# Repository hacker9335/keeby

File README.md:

## Keeby

A custom 98-key mechanical keyboard: KiCad PCB design + QMK/VIA firmware,
built around a Raspberry Pi Pico and an MCP23017 I2C GPIO expander for
extra column pins.

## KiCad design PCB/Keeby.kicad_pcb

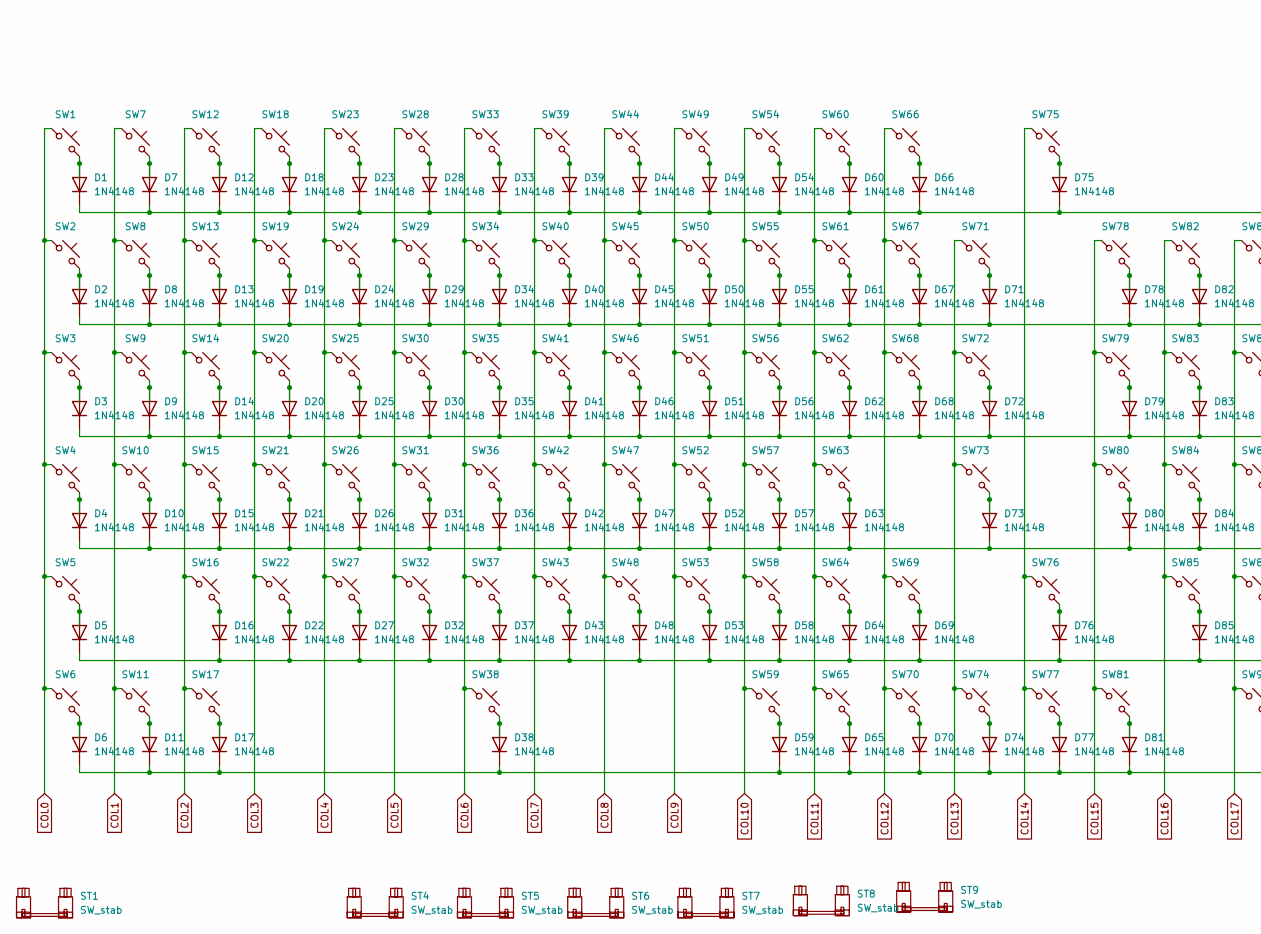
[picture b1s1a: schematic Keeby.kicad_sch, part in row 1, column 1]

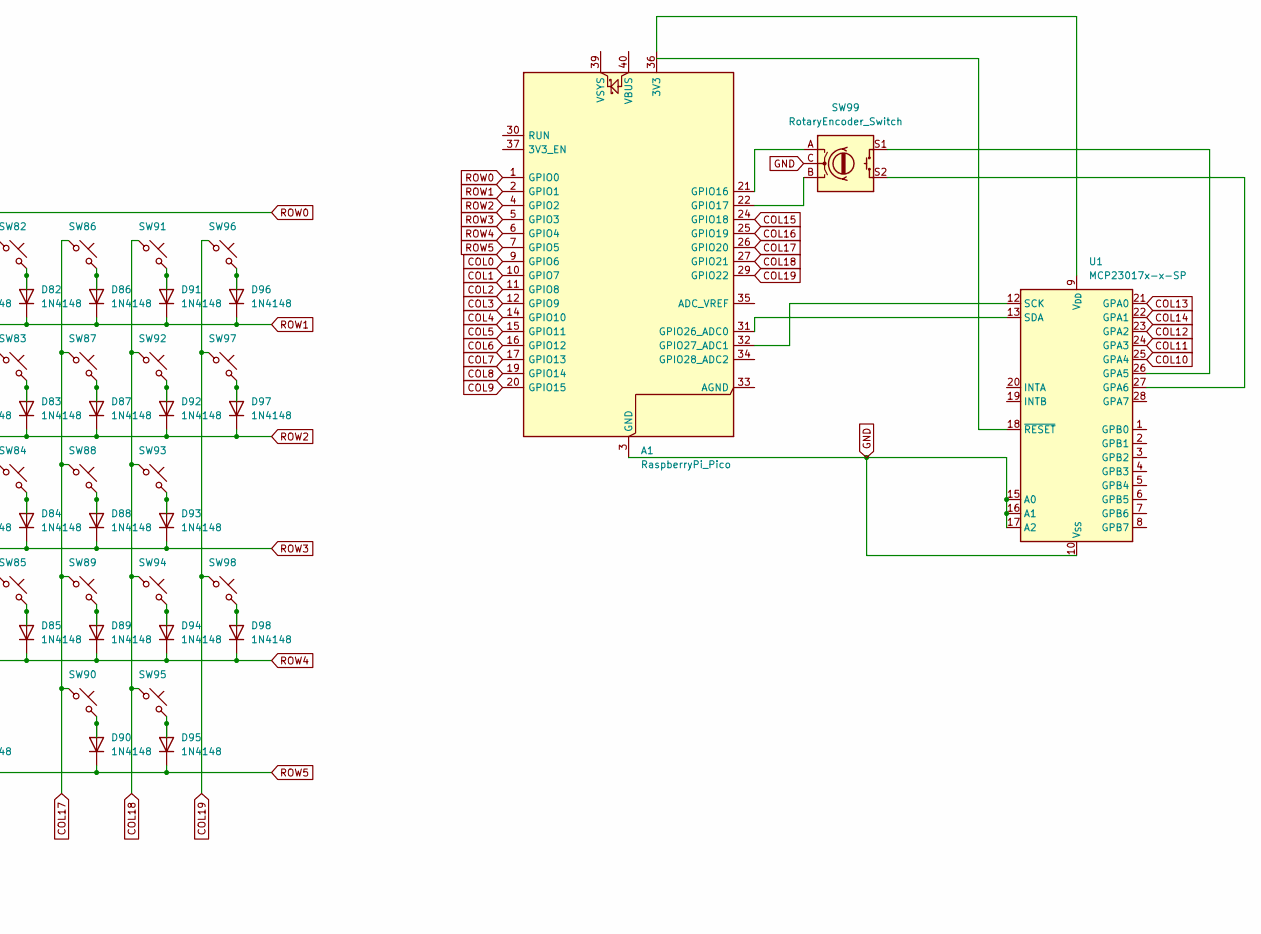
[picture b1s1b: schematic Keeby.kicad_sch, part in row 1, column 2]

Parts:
A1: RaspberryPi_Pico; RaspberryPi_Pico_Common_Unspecified
D1, D2, D3, D4, D5, D6, D7, D8, D9, D10, D11, D12, D13, D14, D15, D16, D17, D18, D19, D20, D21, D22, D23, D24, D25, D26, D27, D28, D29, D30, D31, D32, D33, D34, D35, D36, D37, D38, D39, D40, D41, D42, D43, D44, D45, D46, D47, D48, D49, D50, D51, D52, D53, D54, D55, D56, D57, D58, D59, D60, D61, D62, D63, D64, D65, D66, D67, D68, D69, D70, D71, D72, D73, D74, D75, D76, D77, D78, D79, D80, D81, D82, D83, D84, D85, D86, D87, D88, D89, D90, D91, D92, D93, D94, D95, D96, D97, D98: 1N4148; D_DO-35_SOD27_P7.62mm_Horizontal
ST1, ST4, ST5, ST6, ST7, ST8: SW_stab; STAB_MX_2u
ST9: SW_stab; STAB_MX_6.25u
SW1, SW2, SW3, SW4, SW5, SW6, SW7, SW8, SW9, SW10, SW11, SW12, SW13, SW14, SW15, SW16, SW17, SW18, SW19, SW20, SW21, SW22, SW23, SW24, SW25, SW26, SW27, SW28, SW29, SW30, SW31, SW32, SW33, SW34, SW35, SW36, SW37, SW38, SW39, SW40, SW41, SW42, SW43, SW44, SW45, SW46, SW47, SW48, SW49, SW50, SW51, SW52, SW53, SW54, SW55, SW56, SW57, SW58, SW59, SW60, SW61, SW62, SW63, SW64, SW65, SW66, SW67, SW68, SW69, SW70, SW71, SW72, SW73, SW74, SW75, SW76, SW77, SW78, SW79, SW80, SW81, SW82, SW83, SW84, SW85, SW86, SW87, SW88, SW89, SW90, SW91, SW92, SW93, SW94, SW95, SW96, SW97, SW98: SW_Push; SW_Cherry_MX_1.00u_PCB
SW99: RotaryEncoder_Switch; RotaryEncoder_Alps_EC11E-Switch_Vertical_H20mm_MountingHoles
U1: MCP23017x-x-SP; SSOP-28_5.3x10.2mm_P0.65mm

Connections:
COL0: A1.9 (GPIO6), SW1.1, SW2.1, SW3.1, SW4.1, SW5.1, SW6.1
COL1: A1.10 (GPIO7), SW7.1, SW8.1, SW9.1, SW10.1, SW11.1
COL2: A1.11 (GPIO8), SW12.1, SW13.1, SW14.1, SW15.1, SW16.1, SW17.1
COL3: A1.12 (GPIO9), SW18.1, SW19.1, SW20.1, SW21.1, SW22.1
COL4: A1.14 (GPIO10), SW23.1, SW24.1, SW25.1, SW26.1, SW27.1
COL5: A1.15 (GPIO11), SW28.1, SW29.1, SW30.1, SW31.1, SW32.1
COL6: A1.16 (GPIO12), SW33.1, SW34.1, SW35.1, SW36.1, SW37.1, SW38.1
COL7: A1.17 (GPIO13), SW39.1, SW40.1, SW41.1, SW42.1, SW43.1
COL8: A1.19 (GPIO14), SW44.1, SW45.1, SW46.1, SW47.1, SW48.1
COL9: A1.20 (GPIO15), SW49.1, SW50.1, SW51.1, SW52.1, SW53.1
COL10: SW54.1, SW55.1, SW56.1, SW57.1, SW58.1, SW59.1, U1.25 (GPA4)
COL11: SW60.1, SW61.1, SW62.1, SW63.1, SW64.1, SW65.1, U1.24 (GPA3)
COL12: SW66.1, SW67.1, SW68.1, SW69.1, SW70.1, U1.23 (GPA2)
COL13: SW71.1, SW72.1, SW73.1, SW74.1, U1.21 (GPA0)
COL14: SW75.1, SW76.1, SW77.1, U1.22 (GPA1)
COL15: A1.24 (GPIO18), SW78.1, SW79.1, SW80.1, SW81.1
COL16: A1.25 (GPIO19), SW82.1, SW83.1, SW84.1, SW85.1
COL17: A1.26 (GPIO20), SW86.1, SW87.1, SW88.1, SW89.1, SW90.1
COL18: A1.27 (GPIO21), SW91.1, SW92.1, SW93.1, SW94.1, SW95.1
COL19: A1.29 (GPIO22), SW96.1, SW97.1, SW98.1
GND: A1.3 (GND), A1.8 (GND), A1.13 (GND), A1.18 (GND), A1.23 (GND), A1.28 (GND), A1.38 (GND), SW99.C, U1.10 (V_{SS}), U1.15 (A0), U1.16 (A1), U1.17 (A2)
unnamed: A1.36 (3V3), U1.9 (V_{DD})
unnamed: A1.21 (GPIO16), SW99.A
unnamed: A1.22 (GPIO17), SW99.B
unnamed: A1.31 (GPIO26_ADC0), U1.13 (SDA)
unnamed: A1.32 (GPIO27_ADC1), U1.12 (SCK)
unnamed: D1.2 (A), SW1.2
unnamed: D2.2 (A), SW2.2
unnamed: D3.2 (A), SW3.2
unnamed: D4.2 (A), SW4.2
unnamed: D5.2 (A), SW5.2
unnamed: D6.2 (A), SW6.2
unnamed: D7.2 (A), SW7.2
unnamed: D8.2 (A), SW8.2
unnamed: D9.2 (A), SW9.2
unnamed: D10.2 (A), SW10.2
unnamed: D11.2 (A), SW11.2
unnamed: D12.2 (A), SW12.2
unnamed: D13.2 (A), SW13.2
unnamed: D14.2 (A), SW14.2
unnamed: D15.2 (A), SW15.2
unnamed: D16.2 (A), SW16.2
unnamed: D17.2 (A), SW17.2
unnamed: D18.2 (A), SW18.2
unnamed: D19.2 (A), SW19.2
unnamed: D20.2 (A), SW20.2
unnamed: D21.2 (A), SW21.2
unnamed: D22.2 (A), SW22.2
unnamed: D23.2 (A), SW23.2
unnamed: D24.2 (A), SW24.2
unnamed: D25.2 (A), SW25.2
unnamed: D26.2 (A), SW26.2
unnamed: D27.2 (A), SW27.2
unnamed: D28.2 (A), SW28.2
unnamed: D29.2 (A), SW29.2
unnamed: D30.2 (A), SW30.2
unnamed: D31.2 (A), SW31.2
unnamed: D32.2 (A), SW32.2
unnamed: D33.2 (A), SW33.2
unnamed: D34.2 (A), SW34.2
unnamed: D35.2 (A), SW35.2
unnamed: D36.2 (A), SW36.2
unnamed: D37.2 (A), SW37.2
unnamed: D38.2 (A), SW38.2
unnamed: D39.2 (A), SW39.2
unnamed: D40.2 (A), SW40.2
unnamed: D41.2 (A), SW41.2
unnamed: D42.2 (A), SW42.2
unnamed: D43.2 (A), SW43.2
unnamed: D44.2 (A), SW44.2
unnamed: D45.2 (A), SW45.2
unnamed: D46.2 (A), SW46.2
unnamed: D47.2 (A), SW47.2
unnamed: D48.2 (A), SW48.2
unnamed: D49.2 (A), SW49.2
unnamed: D50.2 (A), SW50.2
unnamed: D51.2 (A), SW51.2
unnamed: D52.2 (A), SW52.2
unnamed: D53.2 (A), SW53.2
unnamed: D54.2 (A), SW54.2
unnamed: D55.2 (A), SW55.2
unnamed: D56.2 (A), SW56.2
unnamed: D57.2 (A), SW57.2
unnamed: D58.2 (A), SW58.2
unnamed: D59.2 (A), SW59.2
unnamed: D60.2 (A), SW60.2
unnamed: D61.2 (A), SW61.2
unnamed: D62.2 (A), SW62.2
unnamed: D63.2 (A), SW63.2
unnamed: D64.2 (A), SW64.2
unnamed: D65.2 (A), SW65.2
unnamed: D66.2 (A), SW66.2
unnamed: D67.2 (A), SW67.2
unnamed: D68.2 (A), SW68.2
unnamed: D69.2 (A), SW69.2
unnamed: D70.2 (A), SW70.2
unnamed: D71.2 (A), SW71.2
unnamed: D72.2 (A), SW72.2
unnamed: D73.2 (A), SW73.2
unnamed: D74.2 (A), SW74.2
unnamed: D75.2 (A), SW75.2
unnamed: D76.2 (A), SW76.2
unnamed: D77.2 (A), SW77.2
unnamed: D78.2 (A), SW78.2
unnamed: D79.2 (A), SW79.2
unnamed: D80.2 (A), SW80.2
unnamed: D81.2 (A), SW81.2
unnamed: D82.2 (A), SW82.2
unnamed: D83.2 (A), SW83.2
unnamed: D84.2 (A), SW84.2
unnamed: D85.2 (A), SW85.2
unnamed: D86.2 (A), SW86.2
unnamed: D87.2 (A), SW87.2
unnamed: D88.2 (A), SW88.2
unnamed: D89.2 (A), SW89.2
unnamed: D90.2 (A), SW90.2
unnamed: D91.2 (A), SW91.2
unnamed: D92.2 (A), SW92.2
unnamed: D93.2 (A), SW93.2
unnamed: D94.2 (A), SW94.2
unnamed: D95.2 (A), SW95.2
unnamed: D96.2 (A), SW96.2
unnamed: D97.2 (A), SW97.2
unnamed: D98.2 (A), SW98.2
unnamed: SW99.S1, U1.26 (GPA5)
unnamed: SW99.S2, U1.27 (GPA6)
ROW0: A1.1 (GPIO0), D1.1 (K), D7.1 (K), D12.1 (K), D18.1 (K), D23.1 (K), D28.1 (K), D33.1 (K), D39.1 (K), D44.1 (K), D49.1 (K), D54.1 (K), D60.1 (K), D66.1 (K), D75.1 (K)
ROW1: A1.2 (GPIO1), D2.1 (K), D8.1 (K), D13.1 (K), D19.1 (K), D24.1 (K), D29.1 (K), D34.1 (K), D40.1 (K), D45.1 (K), D50.1 (K), D55.1 (K), D61.1 (K), D67.1 (K), D71.1 (K), D78.1 (K), D82.1 (K), D86.1 (K), D91.1 (K), D96.1 (K)
ROW2: A1.4 (GPIO2), D3.1 (K), D9.1 (K), D14.1 (K), D20.1 (K), D25.1 (K), D30.1 (K), D35.1 (K), D41.1 (K), D46.1 (K), D51.1 (K), D56.1 (K), D62.1 (K), D68.1 (K), D72.1 (K), D79.1 (K), D83.1 (K), D87.1 (K), D92.1 (K), D97.1 (K)
ROW3: A1.5 (GPIO3), D4.1 (K), D10.1 (K), D15.1 (K), D21.1 (K), D26.1 (K), D31.1 (K), D36.1 (K), D42.1 (K), D47.1 (K), D52.1 (K), D57.1 (K), D63.1 (K), D73.1 (K), D80.1 (K), D84.1 (K), D88.1 (K), D93.1 (K)
ROW4: A1.6 (GPIO4), D5.1 (K), D16.1 (K), D22.1 (K), D27.1 (K), D32.1 (K), D37.1 (K), D43.1 (K), D48.1 (K), D53.1 (K), D58.1 (K), D64.1 (K), D69.1 (K), D76.1 (K), D85.1 (K), D89.1 (K), D94.1 (K), D98.1 (K)
ROW5: A1.7 (GPIO5), D6.1 (K), D11.1 (K), D17.1 (K), D38.1 (K), D59.1 (K), D65.1 (K), D70.1 (K), D74.1 (K), D77.1 (K), D81.1 (K), D90.1 (K), D95.1 (K)

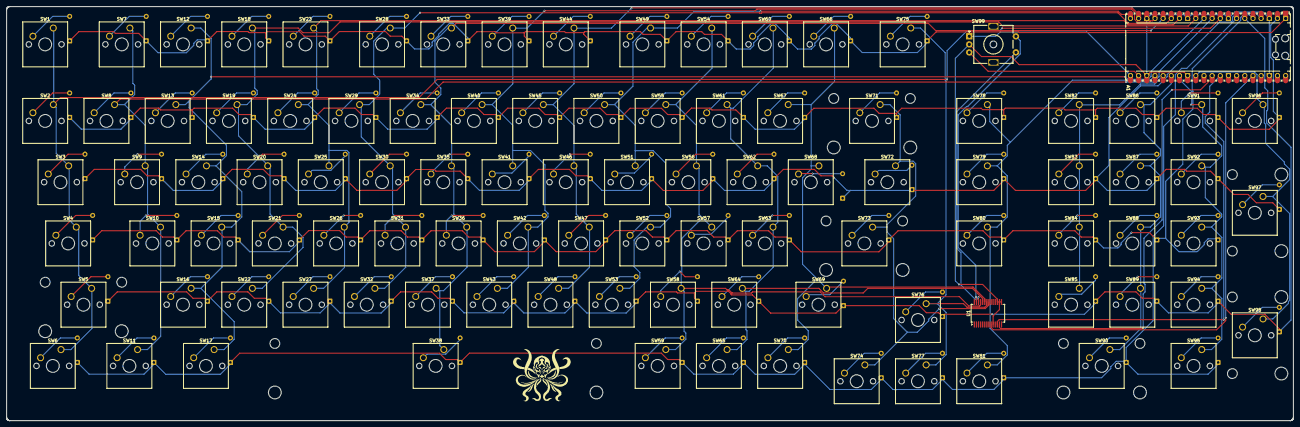
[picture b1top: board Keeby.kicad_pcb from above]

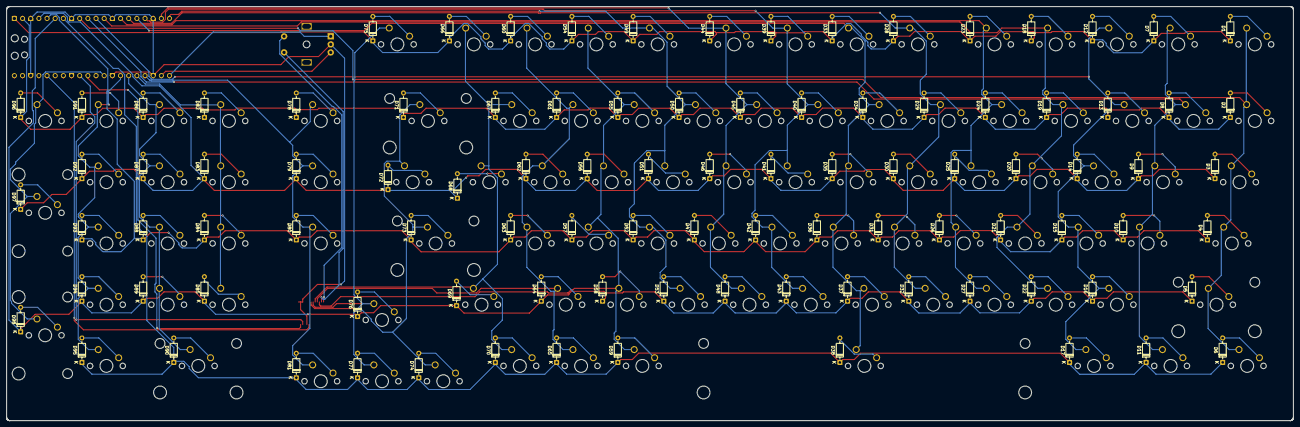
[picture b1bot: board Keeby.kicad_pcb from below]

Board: 2 copper layers, 400.2 x 128.8 mm, 206 parts (98 on the bottom side), 132 nets.

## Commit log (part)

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2026-06-28 Update README with journal entry and layout details
    Added initial journal entry and image to README.
